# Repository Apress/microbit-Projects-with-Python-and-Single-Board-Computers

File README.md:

# Apress Source Code

This repository accompanies [*micro:bit Projects with Python and Single Board Computers: Building STEAM Projects with Code Club and Maker Groups*](https://www.link.springer.com/book/10.1007/9781484291962) by Martin Tan (Apress, 2023).

[comment]: #cover

Download the files as a zip using the green button, or clone the repository to your machine using Git.

## Releases

Release v1.0 corresponds to the code in the published book, without corrections or updates.

## Contributions

See the file Contributing.md for more information on how you can contribute to this repository.

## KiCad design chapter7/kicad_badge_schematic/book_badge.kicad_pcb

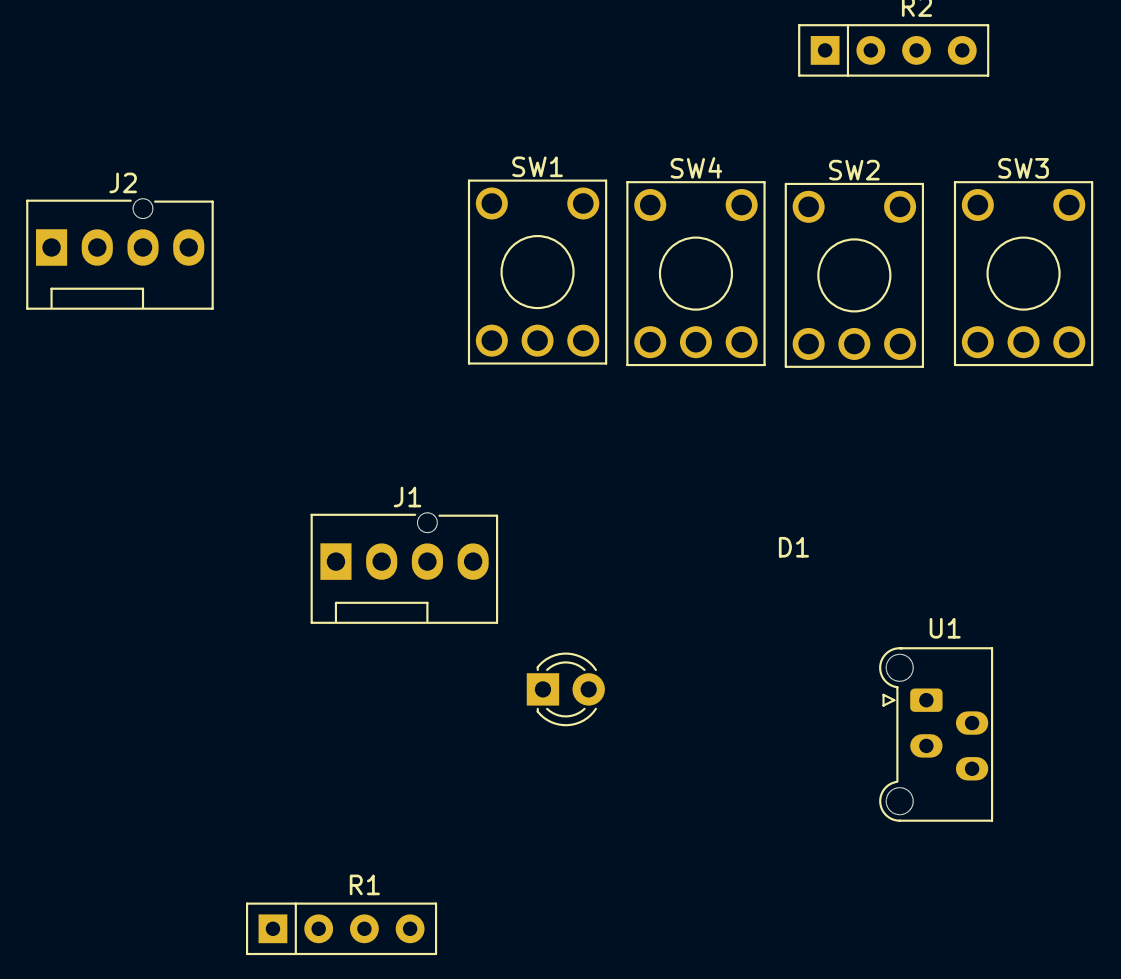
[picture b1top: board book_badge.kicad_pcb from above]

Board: 2 copper layers, 10 parts (0 on the bottom side), 6 nets, no tracks yet.

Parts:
D1: LED; LED_D3.0mm
J1, J2: Conn_01x04_Female; FanPinHeader_1x04_P2.54mm_Vertical
R1, R2: R; R_Array_SIP4
SW1, SW2, SW3, SW4: SW_SPST; KSA_Tactile_SPST
U1: Pico; Molex_Picoflex_90325-0004_2x02_P1.27mm_Vertical

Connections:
unnamed: D1.2 (A), R2.1
unnamed: J1.3, J2.4, R1.1
unnamed: J1.4, J2.1, J2.2, R1.2
unnamed: D1.1 (K), SW1.1 (A), SW2.1 (A), SW3.1 (A), SW4.1 (A), U1.3 (GND)
unnamed: SW1.2 (B), U1.4 (GPIO2)
unnamed: R2.2, U1.1 (GPIO0)
